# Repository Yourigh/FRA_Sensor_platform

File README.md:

# FRA Sensor platform
Analog and Digital datalogger with 16 analog channels (16bit) with programmable gain amplifier (auto ranged from 0-256mV to 0-5V).

# Main board picture

# Development tools
Built on ESP32 module and Arduino framework using Platformio IDE.

# Firmware download to ESP32
https://www.espressif.com/en/products/hardware/esp32/resources

Tools -> Flash Download Tool

Built binary files with the guide are located here:

https://github.com/Yourigh/FRA_Sensor_platform/tree/master/3-FW_SW/1-FW_device/Programming_procedure

Update the esptool.py to newest from:

https://github.com/espressif/esptool

# Resources
https://github.com/greiman/SdFat

https://github.com/jrowberg/i2cdevlib/tree/master/Arduino/ADS1115

https://github.com/8-DK/EtherCard

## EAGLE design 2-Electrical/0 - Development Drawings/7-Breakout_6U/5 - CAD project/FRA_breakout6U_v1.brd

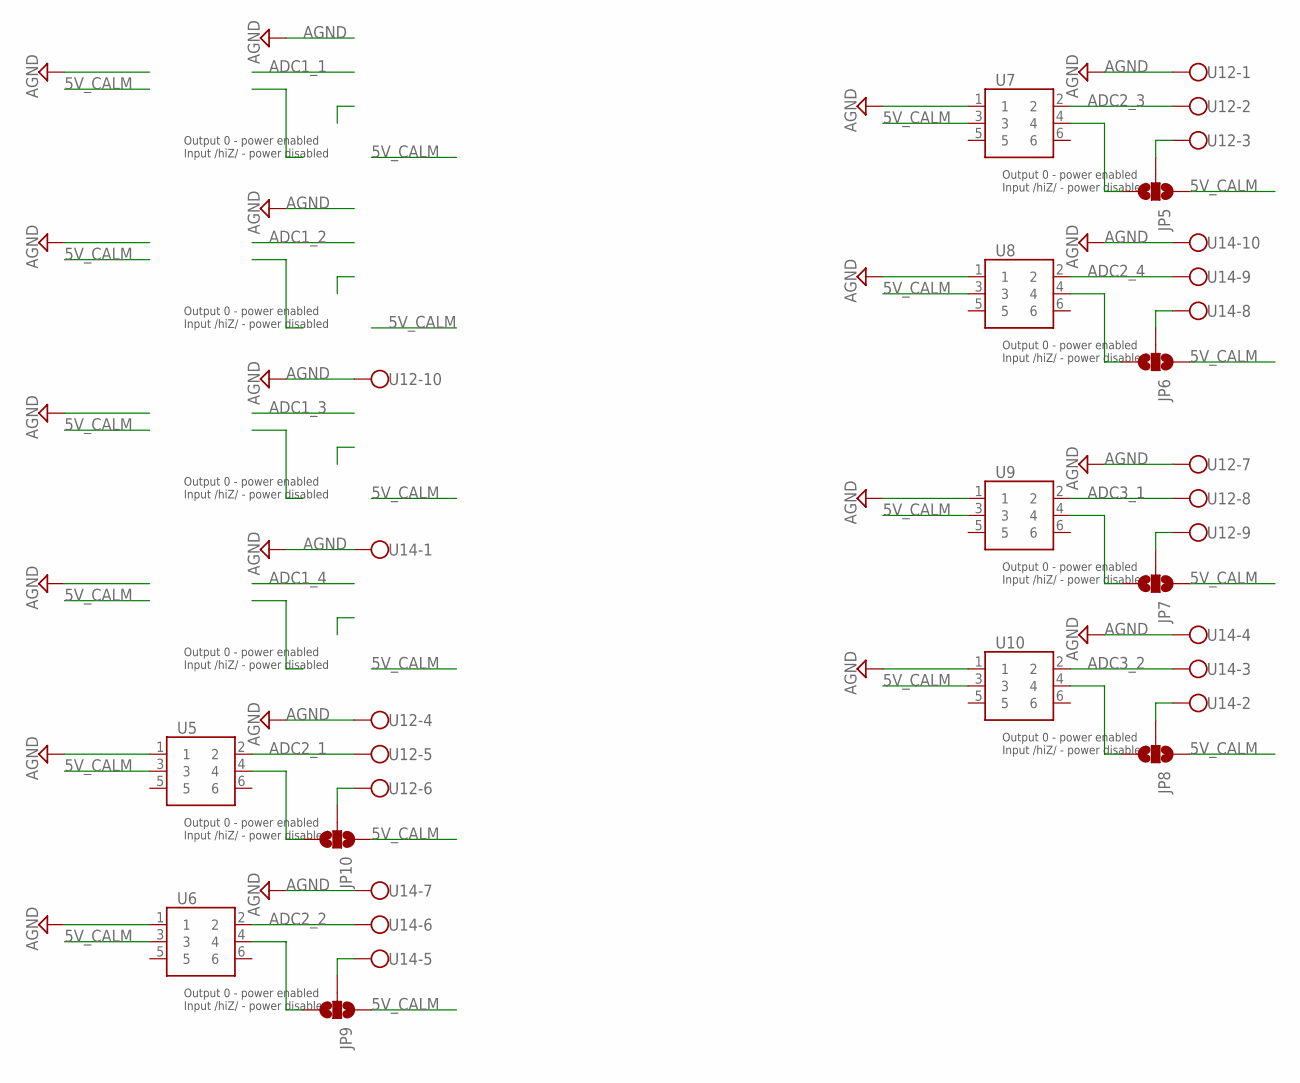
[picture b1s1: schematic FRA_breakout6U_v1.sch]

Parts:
JP5, JP6, JP7, JP8, JP9, JP10: JUMPER-SMT_3_NO_NO_SILK; SMT-JUMPER_3_0-NO_TRACE_NO-SILK
U5, U6, U7, U8, U9, U10: SSW-103-01-F-D; SHDR6W79P254_2X3_813X495X851P; PARTNO 61200621621
U12, U14: TB003V-500-P10BE

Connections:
5V_CALM: JP5.1, JP6.1, JP7.1, JP8.1, JP9.1, JP10.1, U5.3, U6.3, U7.3, U8.3, U9.3, U10.3
ADC2_1: U5.2, U12.5
ADC2_2: U6.2, U14.6
ADC2_3: U7.2, U12.2
ADC2_4: U8.2, U14.9
ADC3_1: U9.2, U12.8
ADC3_2: U10.2, U14.3
AGND: U5.1, U6.1, U7.1, U8.1, U9.1, U10.1, U12.1, U12.4, U12.7, U12.10, U14.1, U14.4, U14.7, U14.10
unnamed: JP5.2, U12.3
unnamed: JP5.3, U7.4
unnamed: JP6.2, U14.8
unnamed: JP6.3, U8.4
unnamed: JP7.2, U12.9
unnamed: JP7.3, U9.4
unnamed: JP8.2, U14.2
unnamed: JP8.3, U10.4
unnamed: JP9.2, U14.5
unnamed: JP9.3, U6.4
unnamed: JP10.2, U12.6
unnamed: JP10.3, U5.4

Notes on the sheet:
Output 0 - power enabled Input /hiZ/ - power disabled

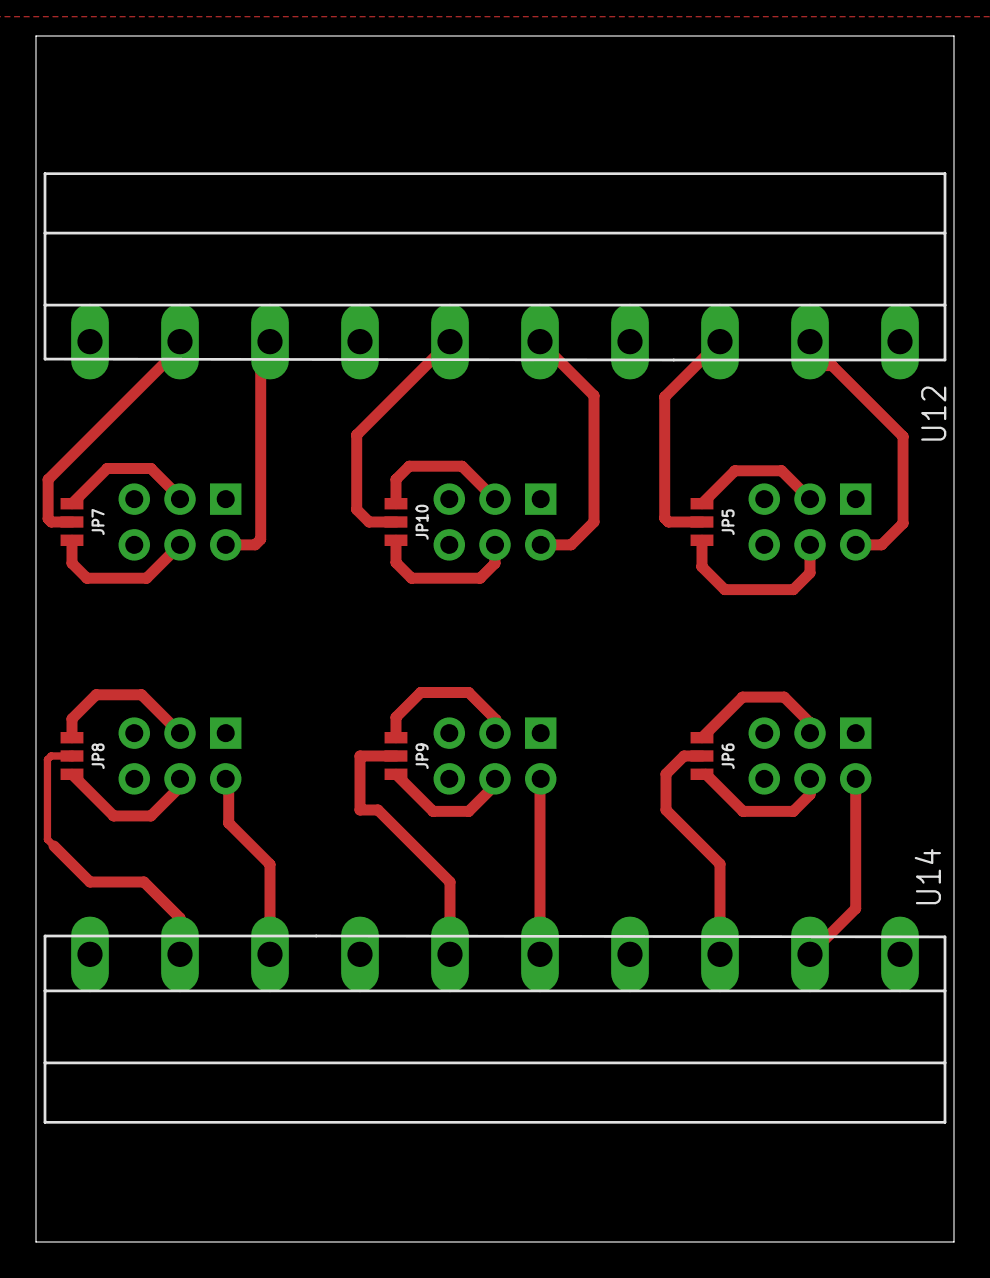
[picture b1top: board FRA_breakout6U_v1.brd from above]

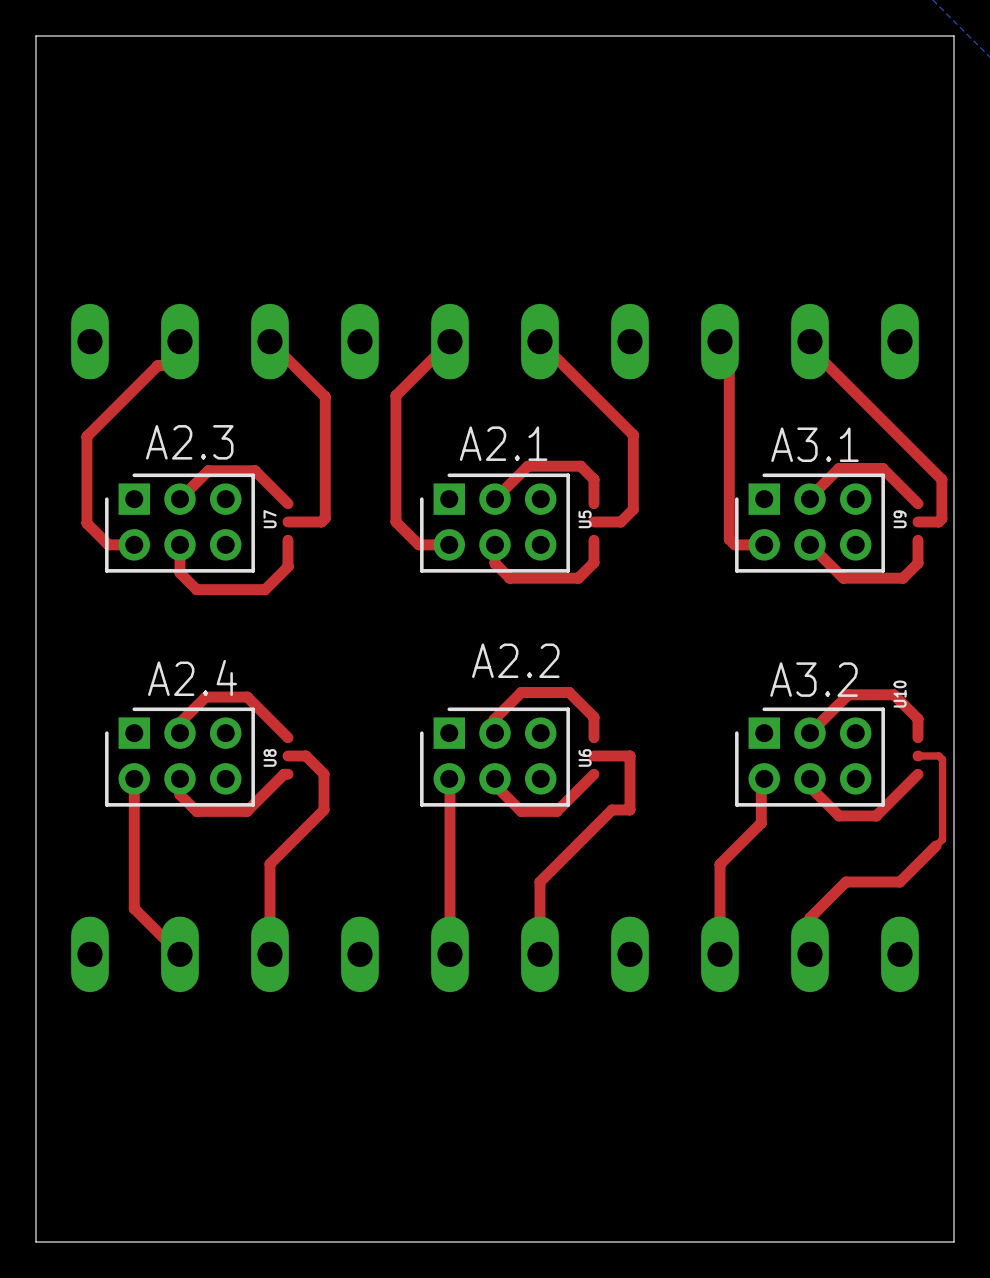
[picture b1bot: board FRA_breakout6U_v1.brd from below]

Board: 2 copper layers, 51.0 x 67.0 mm, 14 parts (6 on the bottom side), 20 nets.

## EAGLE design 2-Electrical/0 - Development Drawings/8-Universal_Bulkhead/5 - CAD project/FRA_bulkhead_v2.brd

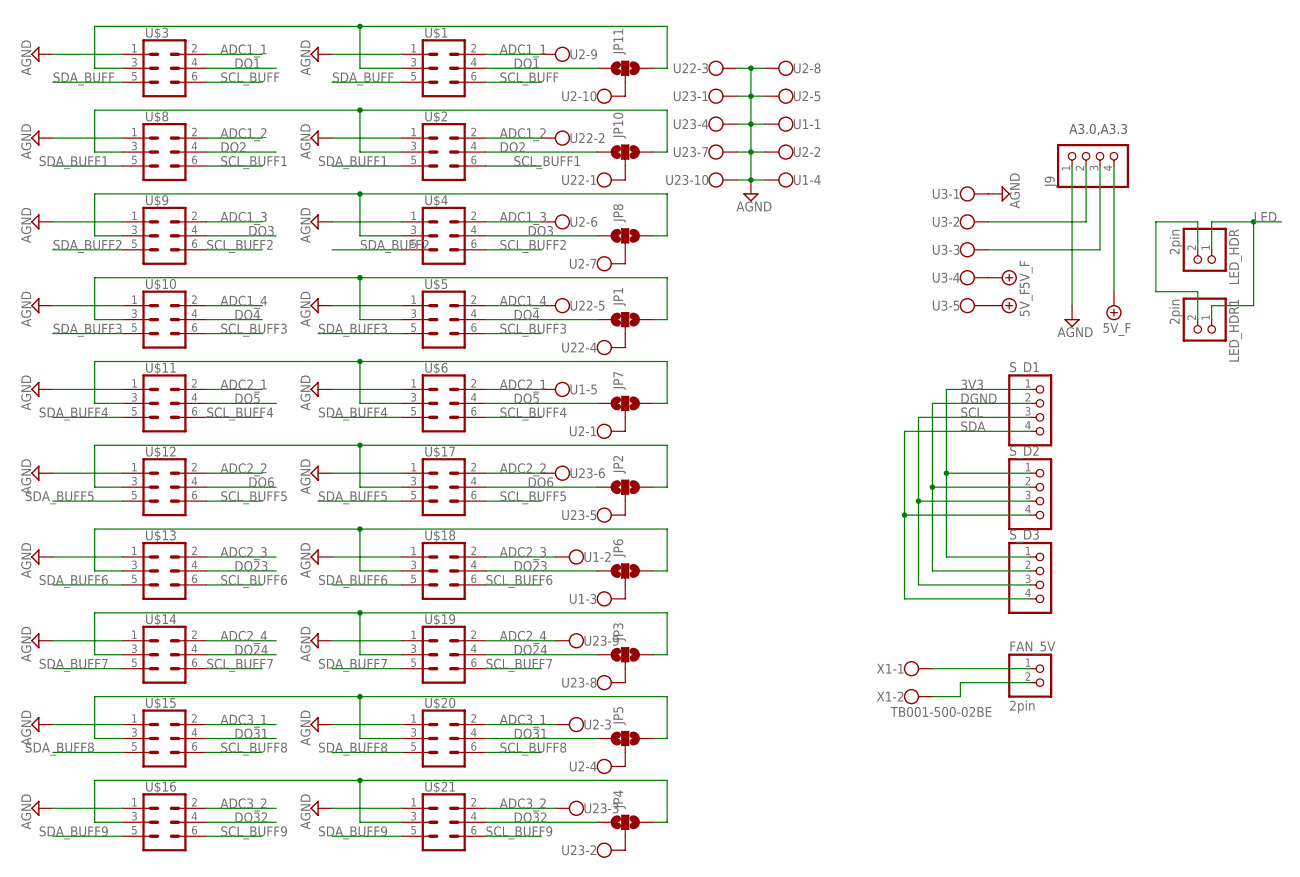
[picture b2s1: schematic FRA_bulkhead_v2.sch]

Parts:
FAN_5V: 2pin; 1X02; PARTNO TSW-102-07-G-S
J9: 4pin; 1X04; PARTNO 61300411121
JP1, JP2, JP3, JP4, JP5, JP6, JP7, JP8, JP10, JP11: JUMPER-SMT_3_NO_NO_SILK; SMT-JUMPER_3_0-NO_TRACE_NO-SILK
LED_HDR, LED_HDR1: 2pin; 1X02; PARTNO TSW-102-07-G-S
S_D1, S_D2, S_D3: 4pin; 1X04; PARTNO 61300411121
U1, U3, U22: TB003V-500-P05BERIGHTANGLE-NORMAL; TB003-500-P05BE
U2, U23: TB003V-500-P10BERIGHTANGLE-NORMAL; TB003-500-P10BE
U$1, U$2, U$3, U$4, U$5, U$6, U$8, U$9, U$10, U$11, U$12, U$13, U$14, U$15, U$16, U$17, U$18, U$19, U$20, U$21: CONN_03X2_WE_61200621621; WE_61200621621; PARTNO 61200621621
X1: TB001-500-02BE; W237-102; PARTNO TB001-500-02BE

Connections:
3V3: S_D1.1, S_D2.1, S_D3.1
+5V/1: J9.4, U3.4, U3.5
ADC1_1: U2.9, U$1.2, U$3.2
ADC1_2: U22.2, U$2.2, U$8.2
ADC1_3: U2.6, U$4.2, U$9.2
ADC1_4: U22.5, U$5.2, U$10.2
ADC2_1: U1.5, U$6.2, U$11.2
ADC2_2: U23.6, U$12.2, U$17.2
ADC2_3: U1.2, U$13.2, U$18.2
ADC2_4: U23.9, U$14.2, U$19.2
ADC3_1: U2.3, U$15.2, U$20.2
ADC3_2: U23.3, U$16.2, U$21.2
AGND: J9.1, U1.1, U1.4, U2.2, U2.5, U2.8, U3.1, U22.3, U23.1, U23.4, U23.7, U23.10, U$1.1, U$2.1, U$3.1, U$4.1, U$5.1, U$6.1, U$8.1, U$9.1, U$10.1, U$11.1, U$12.1, U$13.1, U$14.1, U$15.1, U$16.1, U$17.1, U$18.1, U$19.1, U$20.1, U$21.1
DGND: S_D1.2, S_D2.2, S_D3.2
DO1: JP11.1, U$1.4, U$3.4
DO2: JP10.1, U$2.4, U$8.4
DO3: JP8.1, U$4.4, U$9.4
DO4: JP1.1, U$5.4, U$10.4
DO5: JP7.1, U$6.4, U$11.4
DO6: JP2.1, U$12.4, U$17.4
DO23: JP6.1, U$13.4, U$18.4
DO24: JP3.1, U$14.4, U$19.4
DO31: JP5.1, U$15.4, U$20.4
DO32: JP4.1, U$16.4, U$21.4
LED: LED_HDR.1, LED_HDR1.1
unnamed: FAN_5V.1, X1.1
unnamed: FAN_5V.2, X1.2
unnamed: JP1.2, U22.4
unnamed: JP2.2, U23.5
unnamed: JP3.2, U23.8
unnamed: JP4.2, U23.2
unnamed: JP10.2, U22.1
unnamed: JP11.2, U2.10
unnamed: JP8.2, U2.7
unnamed: JP5.2, U2.4
unnamed: JP7.2, U2.1
unnamed: JP6.2, U1.3
unnamed: JP11.3, U$1.3, U$3.3
unnamed: J9.3, U3.3
unnamed: JP10.3, U$2.3, U$8.3
unnamed: J9.2, U3.2
unnamed: JP8.3, U$4.3, U$9.3
unnamed: JP1.3, U$5.3, U$10.3
unnamed: JP7.3, U$6.3, U$11.3
unnamed: JP2.3, U$12.3, U$17.3
unnamed: JP6.3, U$13.3, U$18.3
unnamed: JP3.3, U$14.3, U$19.3
unnamed: JP5.3, U$15.3, U$20.3
unnamed: JP4.3, U$16.3, U$21.3
unnamed: LED_HDR.2, LED_HDR1.2
SCL: S_D1.3, S_D2.3, S_D3.3
SCL_BUFF: U$1.6, U$3.6
SCL_BUFF1: U$2.6, U$8.6
SCL_BUFF2: U$4.6, U$9.6
SCL_BUFF3: U$5.6, U$10.6
SCL_BUFF4: U$6.6, U$11.6
SCL_BUFF5: U$12.6, U$17.6
SCL_BUFF6: U$13.6, U$18.6
SCL_BUFF7: U$14.6, U$19.6
SCL_BUFF8: U$15.6, U$20.6
SCL_BUFF9: U$16.6, U$21.6
SDA: S_D1.4, S_D2.4, S_D3.4
SDA_BUFF: U$1.5, U$3.5
SDA_BUFF1: U$2.5, U$8.5
SDA_BUFF2: U$4.5, U$9.5
SDA_BUFF3: U$5.5, U$10.5
SDA_BUFF4: U$6.5, U$11.5
SDA_BUFF5: U$12.5, U$17.5
SDA_BUFF6: U$13.5, U$18.5
SDA_BUFF7: U$14.5, U$19.5
SDA_BUFF8: U$15.5, U$20.5
SDA_BUFF9: U$16.5, U$21.5

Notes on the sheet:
A3.0,A3.3

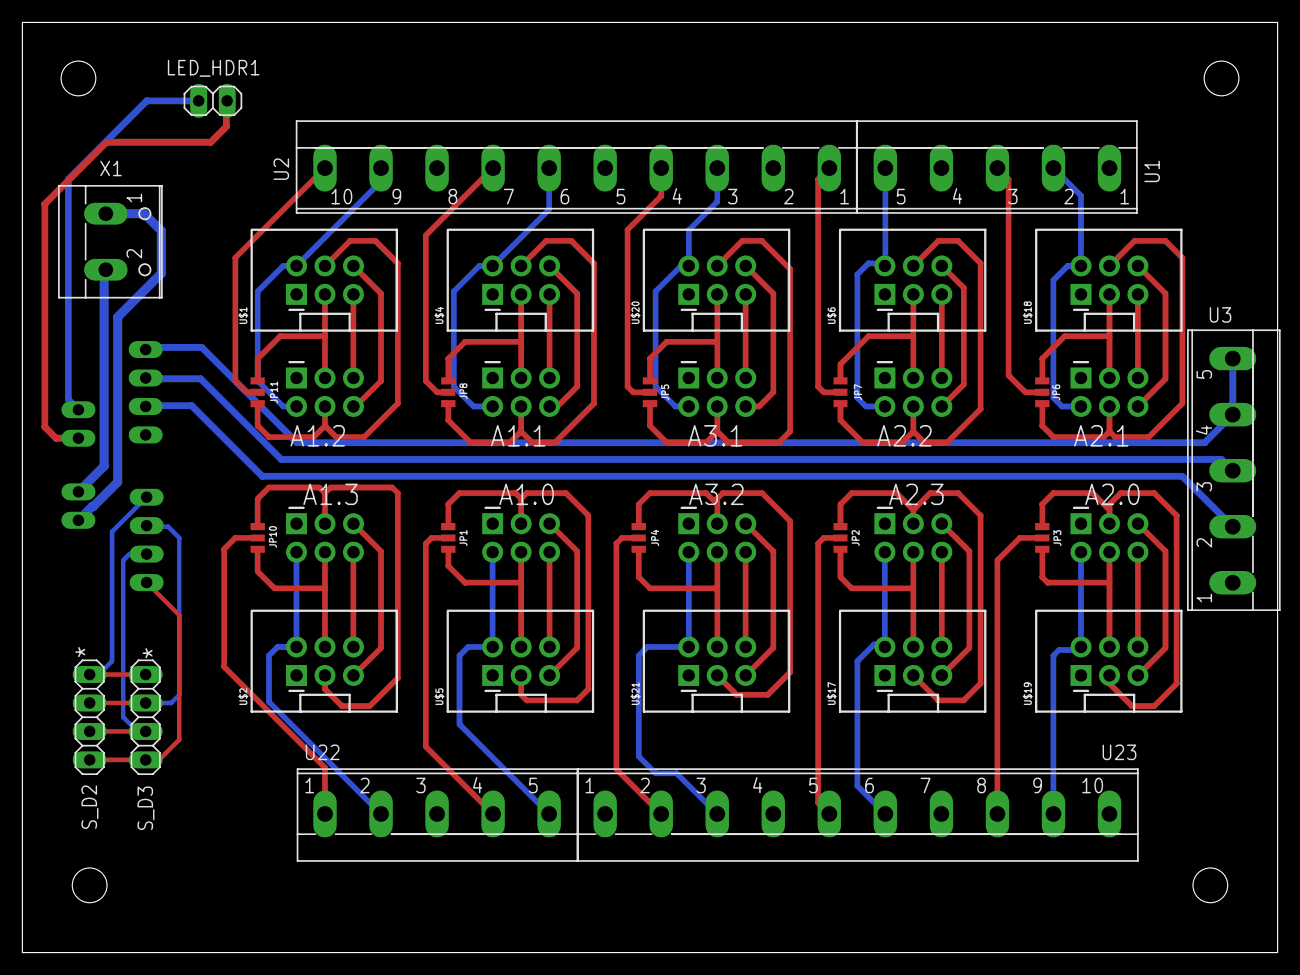
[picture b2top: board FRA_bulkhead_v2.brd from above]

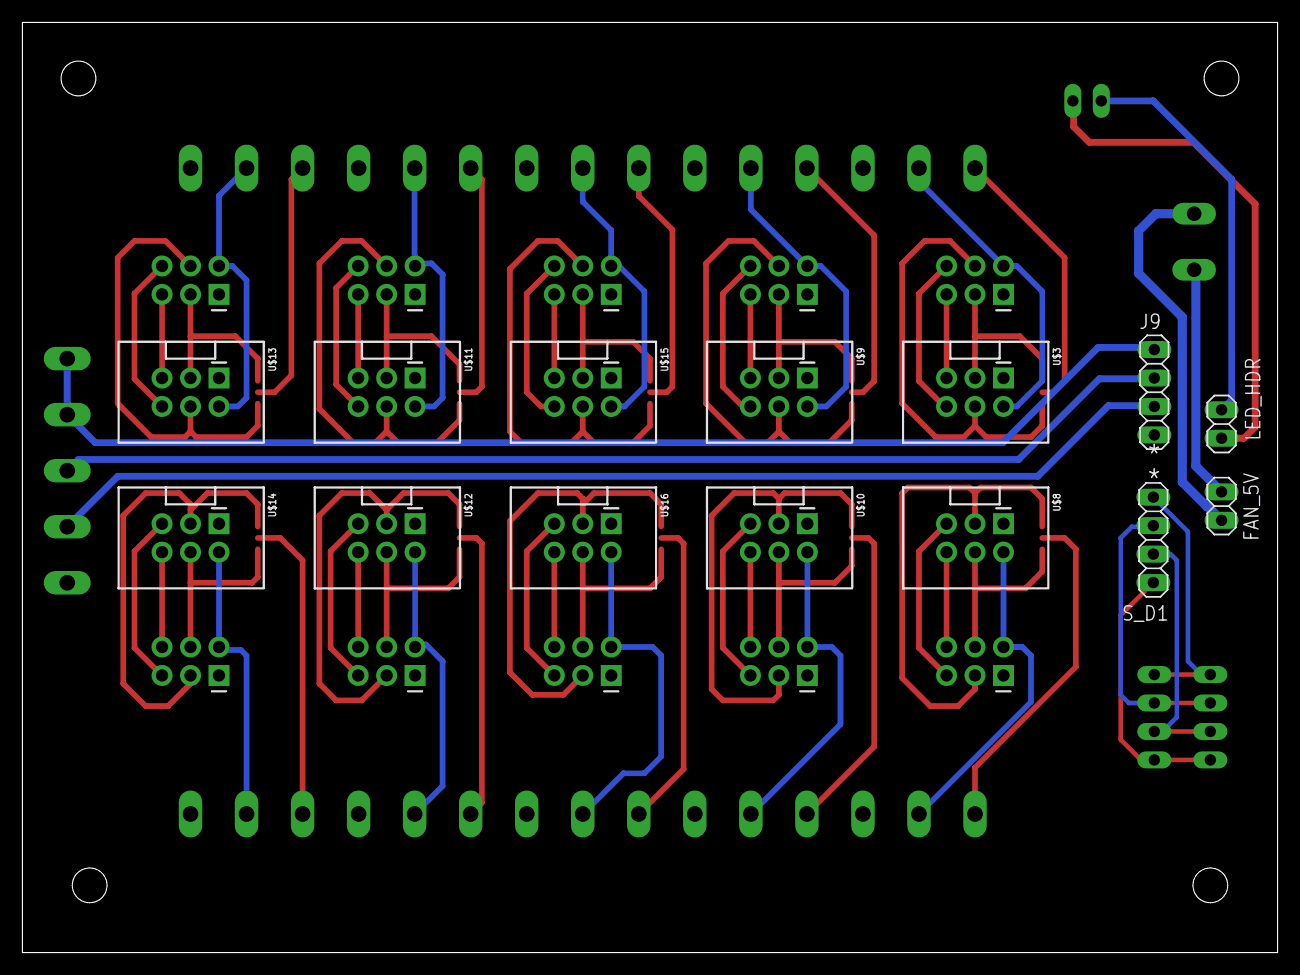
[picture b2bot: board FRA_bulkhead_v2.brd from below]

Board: 2 copper layers, 112.0 x 83.0 mm, 43 parts (14 on the bottom side), 72 nets.

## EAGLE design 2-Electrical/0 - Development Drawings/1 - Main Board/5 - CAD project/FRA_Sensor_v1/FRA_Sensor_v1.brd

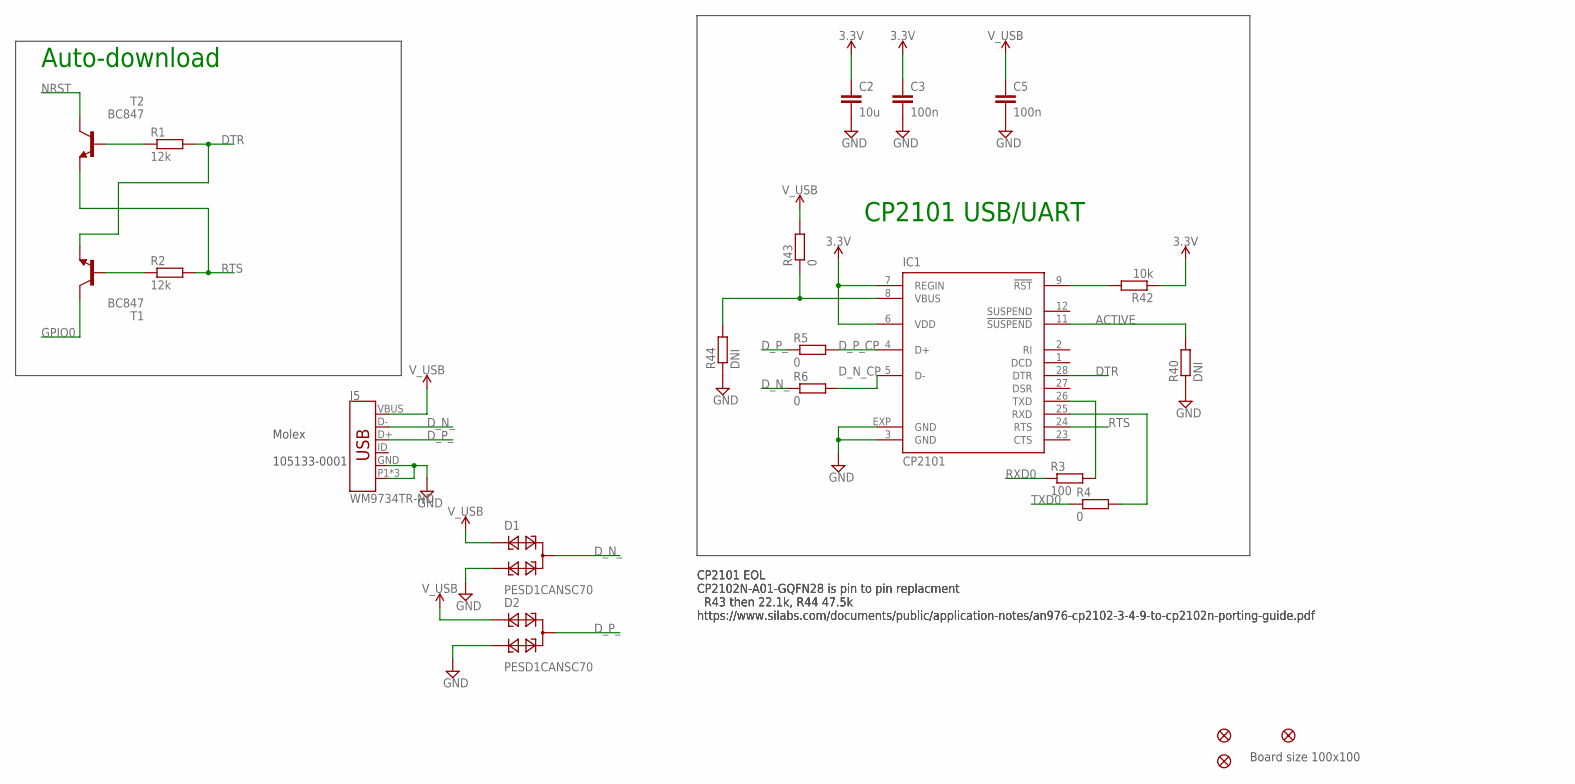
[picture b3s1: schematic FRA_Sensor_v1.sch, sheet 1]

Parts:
C2: 10u; C0603K; PARTNO GRM188R61A106KE69J
C3, C5: 100n; C0603K; PARTNO CC0603KRX7R8BB104
D1, D2: PESD1CANSC70; SOT323-R; PARTNO PESD1CAN-UX
FID1, FID2, FID4: FIDUCIAL""; FIDUCIAL_1MM
IC1: CP2101; MLP28; PARTNO CP2101-GM
J5: WM9734TR-ND; USB-B-MICRO-SMD_VERT; PARTNO 105133-0001
R1, R2: 12k; R0603; PARTNO RC0603FR-0712KL
R3: 100; R0603; PARTNO CRCW0603100RFKEAC
R4, R5, R6, R43: 0; R0603; PARTNO CRCW06030000Z0EAC
R40, R44: DNI; R0603; PARTNO CRCW06030000Z0EAC
R42: 10k; R0603; PARTNO CRCW060310K0JNEAC
T1, T2: BC847; SOT23; PARTNO BC847A-TP

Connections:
3.3V: C2.1, C3.1, IC1.6 (VDD), IC1.7 (REGIN), R42.1; also elsewhere on the board
ACTIVE: IC1.11 (!SUSPEND), R40.2
DTR: IC1.28 (DTR), R1.2, T1.2 (E)
D_N_: D1.3, J5.D-, R6.1
D_N_CP: IC1.5 (D-), R6.2
D_P_: D2.3, J5.D+, R5.1
D_P_CP: IC1.4 (D+), R5.2
GND: C2.2, C3.2, C5.2, D1.2, D2.2, IC1.3 (GND), IC1.EXP (GND), J5.GND, J5.P1 (SHIELD), J5.P2 (SHIELD), J5.P3 (SHIELD), R40.1, R44.1; also elsewhere on the board
GPIO0: T1.3 (C); also elsewhere on the board
unnamed: R1.1, T2.1 (B)
unnamed: R2.1, T1.1 (B)
unnamed: IC1.9 (!RST), R42.2
unnamed: IC1.8 (VBUS), R43.1, R44.2
NRST: T2.3 (C); also elsewhere on the board
RTS: IC1.24 (RTS), R2.2, T2.2 (E)
RXD0: R3.1; also elsewhere on the board
RXD0_CP2101IN: IC1.26 (TXD), R3.2
TXD0: R4.1; also elsewhere on the board
TXD0_CP2101: IC1.25 (RXD), R4.2
V_USB: C5.1, D1.1, D2.1, J5.VBUS, R43.2

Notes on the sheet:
CP2101 USB/UART
Auto-download
Board size 100x100
Molex 105133-0001
CP2101 EOL CP2102N-A01-GQFN28 is pin to pin replacment R43 then 22.1k, R44 47.5k https://www.silabs.com/documents/public/application-notes/an976-cp2102-3-4-9-to-cp2102n-porting-guide.pdf

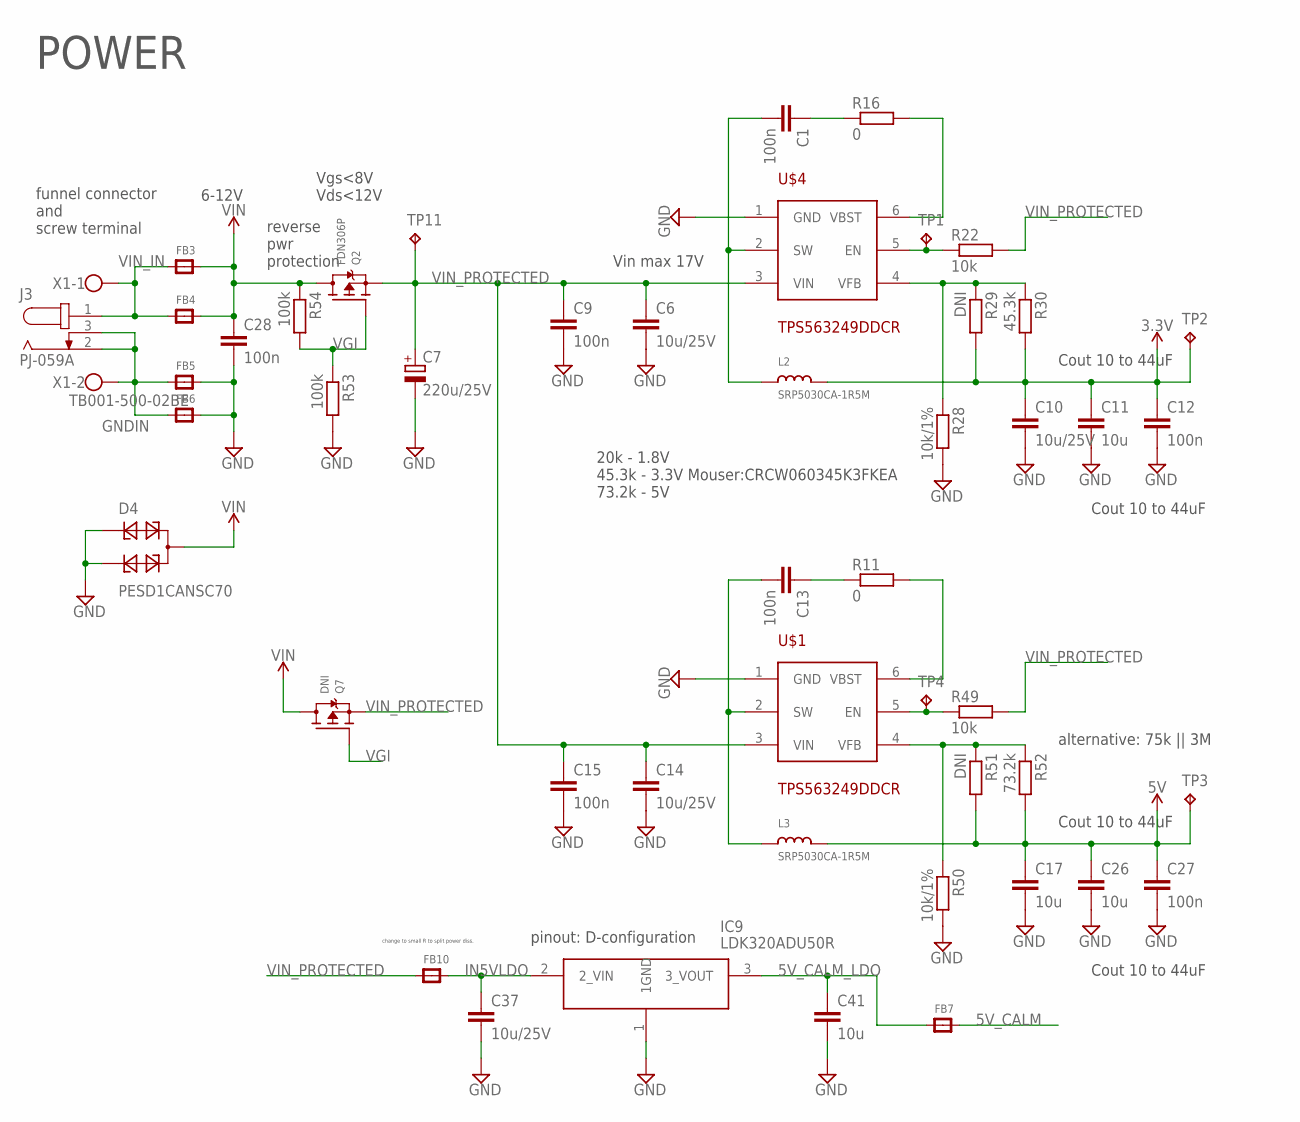
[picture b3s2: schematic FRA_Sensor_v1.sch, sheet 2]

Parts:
C1, C9, C12, C13, C15, C27, C28: 100n; C0603K; PARTNO CC0603KRX7R8BB104
C6, C10, C14, C37: 10u/25V; C0603K; PARTNO GRM188R61E106KA73J
C7: 220u/25V; 153CLV-0605; PARTNO EMZR250ARA221MF80G
C11, C17, C26, C41: 10u; C0603K; PARTNO GRM188R61A106KE69J
D4: PESD1CANSC70; SOT323-R; PARTNO PESD1CAN-UX
FB3, FB4, FB5, FB6, FB7, FB10: FERRITE; 0603; PARTNO BLM18PG121SN1D
IC9: LDK320ADU50R; ST-SOT-89; PARTNO LDK320ADU50R
J3: PJ-059A; PARTNO PJ-059A
L2, L3: SRP5030CA-1R5M; SRP5030CA; PARTNO SRP5030CA-1R5M
Q2: FDN306P; SOT23-WIDE; PARTNO FDN306P
Q7: DNI; TO252
R11, R16: 0; R0603; PARTNO CRCW06030000Z0EAC
R22, R49: 10k; R0603; PARTNO CRCW060310K0JNEAC
R28, R50: 10k/1%; R0603; PARTNO RN73R1JTTD1002D25
R29, R51: DNI; R0603
R30: 45.3k; R0603; PARTNO ERJ-PB3D4532V
R52: 73.2k; R0603; PARTNO ERJ-PB3D7322V
R53, R54: 100k; R0603; PARTNO CRCW0603100KFKEAC
TP1, TP2, TP3, TP4, TP11: TPTP10R; TP10R
U$1, U$4: TPS563249DDCR; SOT23-6; PARTNO TPS563249DDCR
X1: TB001-500-02BE; W237-102; PARTNO TB001-500-02BE

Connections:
3.3V: C10.1, C11.1, C12.1, L2.P$2 (2), R29.2, R30.2, TP2.TP; also elsewhere on the board
5V: C17.1, C26.1, C27.1, L3.P$2 (2), R51.2, R52.2, TP3.TP; also elsewhere on the board
5V_CALM: FB7.2; also elsewhere on the board
5V_CALM_LDO: C41.1, FB7.1, IC9.3 (3_VOUT)
GND: C6.2, C7.-, C9.2, C10.2, C11.2, C12.2, C14.2, C15.2, C17.2, C26.2, C27.2, C28.2, C37.2, C41.2, D4.1, D4.2, FB5.2, FB6.2, IC9.1 (1GND), R28.2, R50.2, R53.2, U$1.1 (GND), U$4.1 (GND); also elsewhere on the board
GNDIN: FB5.1, FB6.1, J3.2, J3.3, X1.2
IN5VLDO: C37.1, FB10.2, IC9.2 (2_VIN)
unnamed: C1.1, R16.1
unnamed: C13.1, R11.1
unnamed: R16.2, U$4.6 (VBST)
unnamed: C1.2, L2.P$1 (1), U$4.2 (SW)
unnamed: R11.2, U$1.6 (VBST)
unnamed: C13.2, L3.P$1 (1), U$1.2 (SW)
unnamed: R49.1, TP4.TP, U$1.5 (EN)
unnamed: R22.1, TP1.TP, U$4.5 (EN)
unnamed: R28.1, R29.1, R30.1, U$4.4 (VFB)
unnamed: R50.1, R51.1, R52.1, U$1.4 (VFB)
VGI: Q2.1 (G), Q7.1 (G), R53.1, R54.2
VIN: C28.1, D4.3, FB3.2, FB4.2, Q2.3 (D), Q7.3 (D), R54.1
VIN_IN: FB3.1, FB4.1, J3.1, X1.1
VIN_PROTECTED: C6.1, C7.+, C9.1, C14.1, C15.1, FB10.1, Q2.2 (S), Q7.2 (S), R22.2, R49.2, TP11.TP, U$1.3 (VIN), U$4.3 (VIN)

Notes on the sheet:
POWER
20k - 1.8V 45.3k - 3.3V Mouser:CRCW060345K3FKEA 73.2k - 5V
Cout 10 to 44uF
reverse pwr protection
Vgs<8V Vds<12V
6-12V
Vin max 17V
funnel connector and screw terminal
change to small R to split power diss.
pinout: D-configuration
alternative: 75k || 3M

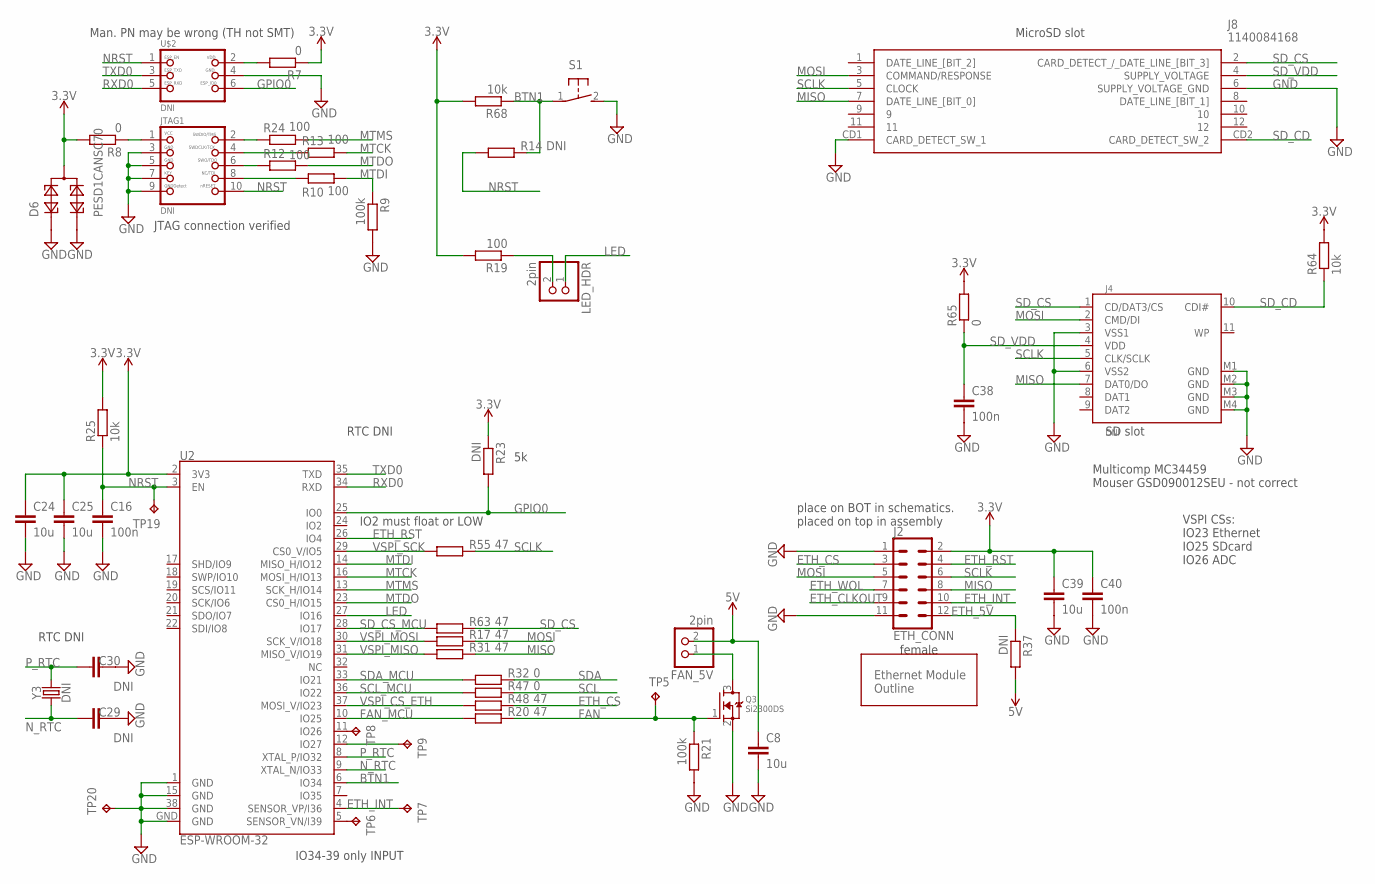
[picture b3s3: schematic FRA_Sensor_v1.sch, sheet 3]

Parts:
C8, C24, C25, C39: 10u; C0603K; PARTNO GRM188R61A106KE69J
C16, C38, C40: 100n; C0603K; PARTNO CC0603KRX7R8BB104
C29, C30: DNI; C0402; PARTNO C0402C220J5GAC7411
D6: PESD1CANSC70; SOT323-R; PARTNO PESD1CAN-UX
FAN_5V: 2pin; 1X02; PARTNO TSW-102-07-G-S
J2: ETH_CONN; 2X6; PARTNO CES-106-01-T-D
J4: DNI; SDCMF-10915W010; PARTNO GSD090012SEU
J8: 1140084168; PARTNO 1140084168
JTAG1: DNI; 2X05_1.27MM_SMT; PARTNO M50-3600542R
LED_HDR: 2pin; 1X02; PARTNO TSW-102-07-G-S
Q3: Si2300DS; SOT23; PARTNO SI2300DS-T1-GE3
R7, R8, R32, R47, R65: 0; R0603; PARTNO CRCW06030000Z0EAC
R9, R21: 100k; R0603; PARTNO CRCW0603100KFKEAC
R10, R12, R13, R19, R24: 100; R0603; PARTNO CRCW0603100RFKEAC
R14, R23, R37: DNI; R0603; PARTNO CRCW06030000Z0EAC
R17, R20, R31, R48, R55, R63: 47; R0603; PARTNO CRCW060347R0FKEAC
R25, R64, R68: 10k; R0603; PARTNO CRCW060310K0JNEAC
S1: 31-XX; B3F-31XX; PARTNO FSMRA5JH
TP5, TP6, TP7, TP8, TP9, TP19, TP20: TPTP10R; TP10R
U2: ESP-WROOM-32; PARTNO ESP32-WROOM-32
U$2: DNI; 2X03_1.27MM_SMT; PARTNO HTMS-103-03-T-D-SM
U$7: ETH_MODULE_OUTLINE; ETH_MODULE_OUTLINE_SMALL
Y3: DNI; CRYSTAL-SMD-3.2X1.5MM; PARTNO FC-135 32.7680KA-A3

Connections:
3.3V: C24.1, C25.1, C39.1, C40.1, D6.3, J2.2, R7.1, R8.2, R19.2, R23.1, R25.2, R64.2, R65.2, R68.2, U2.2 (3V3); also elsewhere on the board
5V: C8.1, FAN_5V.2, R37.2; also elsewhere on the board
BTN1: R14.2, R68.1, S1.1, U2.6 (IO34)
ETH_5V: J2.12, R37.1
ETH_CLKOUT: J2.9
ETH_CS: J2.3, R48.2
ETH_INT: J2.10, TP7.TP, U2.4 (SENSOR_VP/I36)
ETH_RST: J2.4, U2.26 (IO4)
ETH_WOL: J2.7
FAN: Q3.1 (G), R20.2, R21.1, TP5.TP
FAN_MCU: R20.1, U2.10 (IO25)
GND: C8.2, C16.2, C24.2, C25.2, C29.2, C30.2, C38.2, C39.2, C40.2, D6.1, D6.2, J2.1, J2.11, J4.3 (VSS1), J4.6 (VSS2), J4.M1 (GND), J4.M2 (GND), J4.M3 (GND), J4.M4 (GND), J8.6 (SUPPLY_VOLTAGE_GND), J8.CD1 (CARD_DETECT_SW_1), JTAG1.3, JTAG1.5, JTAG1.7, JTAG1.9, Q3.2 (S), R9.2, R21.2, S1.2 (S), TP20.TP, U2.1 (GND), U2.15 (GND), U2.38 (GND), U2.GND, U2.GND1, U2.GND2, U2.GND3, U2.GND4, U2.GND5, U2.GND6, U2.GND7, U2.GND8, U$2.4; also elsewhere on the board
GPIO0: R23.2, U2.25 (IO0), U$2.6; also elsewhere on the board
LED: LED_HDR.1, U2.27 (IO16)
MISO: J2.8, J4.7 (DAT0/DO), J8.7 (DATE_LINE_[BIT_0]), R31.2
MOSI: J2.5, J4.2 (CMD/DI), J8.3 (COMMAND/RESPONSE), R17.2
MTCK: R13.2, U2.16 (MOSI_H/IO13)
MTDI: R9.1, R10.2, U2.14 (MISO_H/IO12)
MTDO: R12.2, U2.23 (CS0_H/IO15)
MTMS: R24.2, U2.13 (SCK_H/IO14)
unnamed: LED_HDR.2, R19.1
unnamed: FAN_5V.1, Q3.3 (D)
unnamed: TP6.TP, U2.5 (SENSOR_VN/I39)
unnamed: TP8.TP, U2.11 (IO26)
unnamed: TP9.TP, U2.12 (IO27)
NRST: C16.1, JTAG1.10, R14.1, R25.1, TP19.TP, U2.3 (EN), U$2.1; also elsewhere on the board
N_RTC: C29.1, U2.9 (XTAL_N/IO33), Y3.P$1 (1)
P_RTC: C30.1, U2.8 (XTAL_P/IO32), Y3.P$2 (2)
RXD0: U2.34 (RXD), U$2.5; also elsewhere on the board
SCL: R47.2; also elsewhere on the board
SCLK: J2.6, J4.5 (CLK/SCLK), J8.5 (CLOCK), R55.2
SCL_MCU: R47.1, U2.36 (IO22)
SDA: R32.2; also elsewhere on the board
SDA_MCU: R32.1, U2.33 (IO21)
SD_CD: J4.10 (CDI#), J8.CD2 (CARD_DETECT_SW_2), R64.1
SD_CS: J4.1 (CD/DAT3/CS), J8.2 (CARD_DETECT_/_DATE_LINE_[BIT_3]), R63.2
SD_CS_MCU: R63.1, U2.28 (IO17)
SD_VDD: C38.1, J4.4 (VDD), J8.4 (SUPPLY_VOLTAGE), R65.1
TCKCONN: JTAG1.4, R13.1
TDICONN: JTAG1.8, R10.1
TDOCONN: JTAG1.6, R12.1
TMSCONN: JTAG1.2, R24.1
TXD0: U2.35 (TXD), U$2.3; also elsewhere on the board
VCCJTAG: JTAG1.1, R8.1
VDDPROG: R7.2, U$2.2
VSPI_CS_ETH: R48.1, U2.37 (MOSI_V/IO23)
VSPI_MISO: R31.1, U2.31 (MISO_V/IO19)
VSPI_MOSI: R17.1, U2.30 (SCK_V/IO18)
VSPI_SCK: R55.1, U2.29 (CS0_V/IO5)

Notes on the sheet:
VSPI CSs: IO23 Ethernet IO25 SDcard IO26 ADC
MicroSD slot
SD slot
JTAG connection verified
IO34-39 only INPUT
place on BOT in schematics. placed on top in assembly
female
RTC DNI
Multicomp MC34459 Mouser GSD090012SEU - not correct
IO2 must float or LOW
Man. PN may be wrong (TH not SMT)

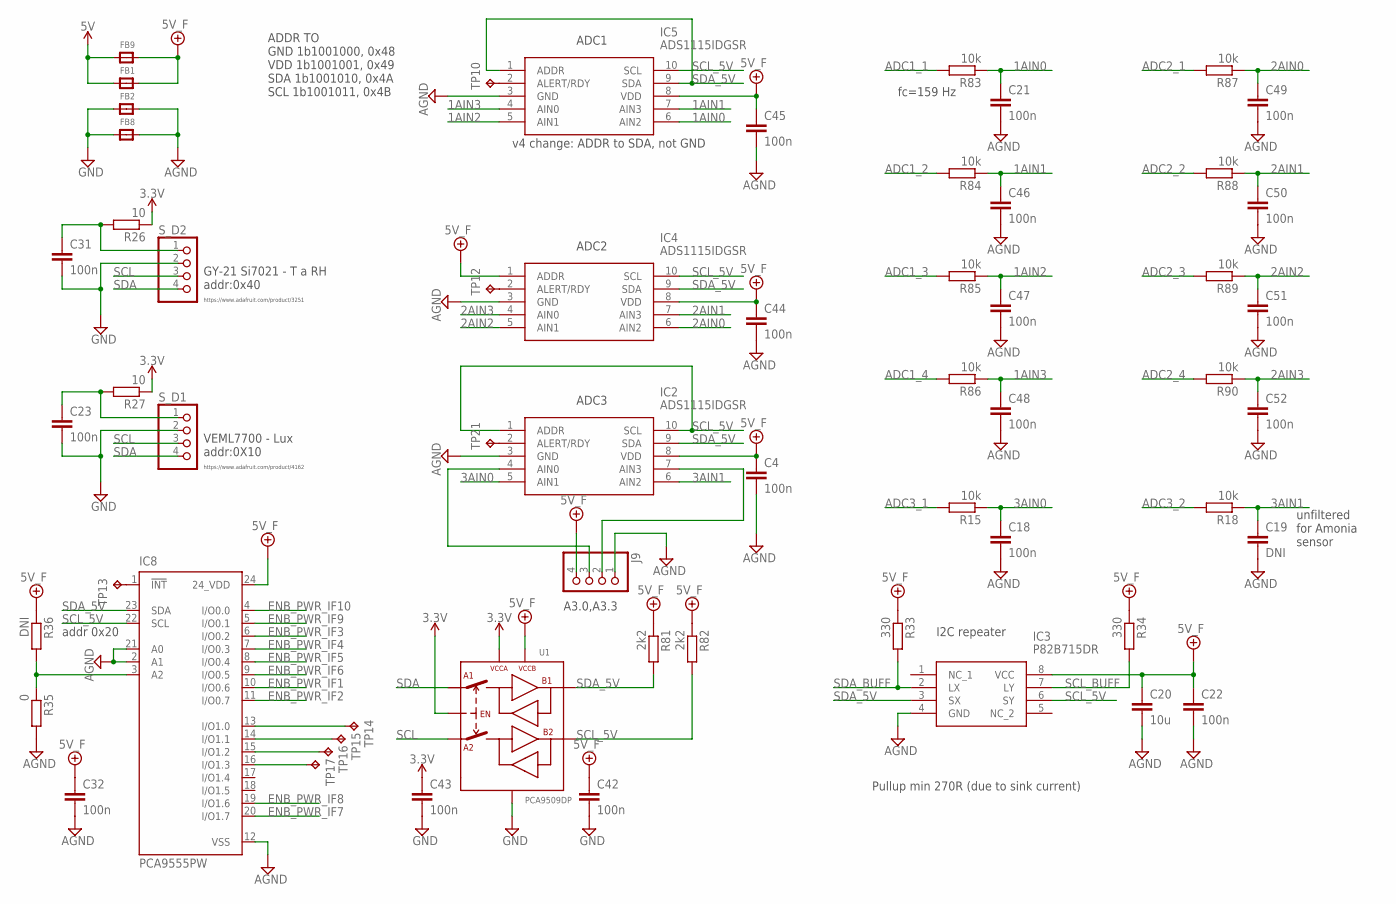
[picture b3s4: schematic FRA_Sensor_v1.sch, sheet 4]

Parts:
C4, C18, C21, C22, C23, C31, C32, C42, C43, C44, C45, C46, C47, C48, C49, C50, C51, C52: 100n; C0603K; PARTNO CC0603KRX7R8BB104
C19: DNI; C0603K; PARTNO CC0603KRX7R8BB104
C20: 10u; C0603K; PARTNO GRM188R61A106KE69J
FB1, FB2, FB8, FB9: FERRITE; 0603; PARTNO BLM18PG121SN1D
IC2, IC4, IC5: ADS1115IDGSR; SOP50P490X110-10N; PARTNO ADS1115IDGSR
IC3: P82B715DR; SOIC127P600X175-8N; PARTNO P82B715DR
IC8: PCA9555PW; TSSOP24; PARTNO PCA9555PW,118
J9: 4pin; 1X04; PARTNO 61300411121
R15, R18, R83, R84, R85, R86, R87, R88, R89, R90: 10k; R0603; PARTNO CRCW060310K0JNEAC
R26, R27: 10; R0603; PARTNO CRCW060310R0FKEAC
R33, R34: 330; R0603; PARTNO CRCW0603330RFKEAC
R35: 0; R0603; PARTNO CRCW06030000Z0EAC
R36: DNI; R0603; PARTNO CRCW0603330RFKEAC
R81, R82: 2k2; R0603; PARTNO RCS06032K20JNEA
S_D1, S_D2: 4pin; 1X04; PARTNO 61300411121
TP10, TP12, TP13, TP14, TP15, TP16, TP17, TP21: TPTP10R; TP10R
U1: PCA9509DP; SOT505-1; PARTNO PCA9509DP,118

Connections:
1AIN0: C21.1, IC5.6 (AIN2), R83.1
1AIN1: C46.1, IC5.7 (AIN3), R84.1
1AIN2: C47.1, IC5.5 (AIN1), R85.1
1AIN3: C48.1, IC5.4 (AIN0), R86.1
2AIN0: C49.1, IC4.6 (AIN2), R87.1
2AIN1: C50.1, IC4.7 (AIN3), R88.1
2AIN2: C51.1, IC4.5 (AIN1), R89.1
2AIN3: C52.1, IC4.4 (AIN0), R90.1
3.3V: C43.1, R26.1, R27.1, U1.1 (VCC(A)), U1.5 (EN); also elsewhere on the board
3AIN0: C18.1, IC2.5 (AIN1), R15.1
3AIN1: C19.1, IC2.6 (AIN2), R18.1
5V: FB1.1, FB9.1; also elsewhere on the board
+5V/1: C4.1, C20.1, C22.1, C32.1, C42.1, C44.1, C45.1, FB1.2, FB9.2, IC2.8 (VDD), IC3.8 (VCC), IC4.1 (ADDR), IC4.8 (VDD), IC5.8 (VDD), IC8.24 (24_VDD), J9.4, R33.1, R34.1, R36.1, R81.1, R82.1, U1.8 (VCC(B)); also elsewhere on the board
ADC1_1: R83.2; also elsewhere on the board
ADC1_2: R84.2; also elsewhere on the board
ADC1_3: R85.2; also elsewhere on the board
ADC1_4: R86.2; also elsewhere on the board
ADC2_1: R87.2; also elsewhere on the board
ADC2_2: R88.2; also elsewhere on the board
ADC2_3: R89.2; also elsewhere on the board
ADC2_4: R90.2; also elsewhere on the board
ADC3_1: R15.2; also elsewhere on the board
ADC3_2: R18.2; also elsewhere on the board
AGND: C4.2, C18.2, C19.2, C20.2, C21.2, C22.2, C32.2, C44.2, C45.2, C46.2, C47.2, C48.2, C49.2, C50.2, C51.2, C52.2, FB2.2, FB8.2, IC2.3 (GND), IC3.4 (GND), IC4.3 (GND), IC5.3 (GND), IC8.2 (A1), IC8.12 (VSS), IC8.21 (A0), J9.1, R35.2; also elsewhere on the board
ENB_PWR_IF1: IC8.10 (I/O0.6); also elsewhere on the board
ENB_PWR_IF2: IC8.11 (I/O0.7); also elsewhere on the board
ENB_PWR_IF3: IC8.6 (I/O0.2); also elsewhere on the board
ENB_PWR_IF4: IC8.7 (I/O0.3); also elsewhere on the board
ENB_PWR_IF5: IC8.8 (I/O0.4); also elsewhere on the board
ENB_PWR_IF6: IC8.9 (I/O0.5); also elsewhere on the board
ENB_PWR_IF7: IC8.20 (I/O1.7); also elsewhere on the board
ENB_PWR_IF8: IC8.19 (I/O1.6); also elsewhere on the board
ENB_PWR_IF9: IC8.5 (I/O0.1); also elsewhere on the board
ENB_PWR_IF10: IC8.4 (I/O0.0); also elsewhere on the board
GND: C23.2, C31.2, C42.2, C43.2, FB2.1, FB8.1, S_D1.2, S_D2.2, U1.4 (GND); also elsewhere on the board
unnamed: C23.1, R27.2, S_D1.1
unnamed: C31.1, R26.2, S_D2.1
unnamed: IC2.2 (ALERT/RDY), TP21.TP
unnamed: IC8.13 (I/O1.0), TP14.TP
unnamed: IC8.14 (I/O1.1), TP15.TP
unnamed: IC8.15 (I/O1.2), TP16.TP
unnamed: IC8.16 (I/O1.3), TP17.TP
unnamed: IC2.4 (AIN0), J9.3
unnamed: IC2.7 (AIN3), J9.2
unnamed: IC8.3 (A2), R35.1, R36.2
unnamed: IC4.2 (ALERT/RDY), TP12.TP
unnamed: IC5.2 (ALERT/RDY), TP10.TP
unnamed: IC8.1 (!INT), TP13.TP
SCL: S_D1.3, S_D2.3, U1.3 (A2); also elsewhere on the board
SCL_5V: IC2.1 (ADDR), IC2.10 (SCL), IC3.6 (SY), IC4.10 (SCL), IC5.10 (SCL), IC8.22 (SCL), R82.2, U1.6 (B2)
SCL_BUFF: IC3.7 (LY), R34.2; also elsewhere on the board
SDA: S_D1.4, S_D2.4, U1.2 (A1); also elsewhere on the board
SDA_5V: IC2.9 (SDA), IC3.3 (SX), IC4.9 (SDA), IC5.1 (ADDR), IC5.9 (SDA), IC8.23 (SDA), R81.2, U1.7 (B1)
SDA_BUFF: IC3.2 (LX), R33.2; also elsewhere on the board

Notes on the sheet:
VEML7700 - Lux addr:0X10
https://www.adafruit.com/product/4162
https://www.adafruit.com/product/3251
ADDR TO GND 1b1001000, 0x48 VDD 1b1001001, 0x49 SDA 1b1001010, 0x4A SCL 1b1001011, 0x4B
addr 0x20
fc=159 Hz
GY-21 Si7021 - T a RH addr:0x40
Pullup min 270R (due to sink current)
I2C repeater
ADC1
ADC2
ADC3
A3.0,A3.3
v4 change: ADDR to SDA, not GND
unfiltered for Amonia sensor

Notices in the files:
3-FW_SW/1-FW_device/FRA_SP_ESP32v2/src/main.cpp:
License: GPLv2
parts and their libraries:
SparkFun-Retired: Licensing: Creative Commons ShareAlike 4.0 International - https://creativecommons.org/licenses/by-sa/4.0
microbuilder: This work is placed in the public domain, and may be freely used for commercial and non-commercial work with the following conditions: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
